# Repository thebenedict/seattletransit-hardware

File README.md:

# Seattle Transit Live

Schematic and PCB for a circuit board map of Seattle area public transit.

[www.seattletransitlive.com](https://www.seattletransitlive.com/)

This board uses an `ESP32-C3` to drive `383` individually addressable `WS2812` LEDs arranged as a stylized regional transit map. The LEDs are split across two chains, and represent live movement across rail, ferry, water taxi, and monorail routes.

## Main Functionality

- Displays a physical transit map with addressable LEDs placed along the network.
- Uses an `ESP32-C3-MINI-1` as the main controller.
- Takes power and USB data over `USB-C`.
- Drives the LED chains through level shifting and a switchable LED power rail.
- Includes an ambient light sensor for auto-dimming in software.

## Repo Contents

- `transit.kicad_sch`, `transit.kicad_pcb`, and the sub-sheet `.kicad_sch` files contain the Rev C schematic and PCB layout.
- `production/` contains fabrication outputs, BOM data, positions, and packaged manufacturing files.
- `tools/` contains scripts and transit GIS/GTFS inputs used to generate LED map configuration data.
- `3d_views/` and `web/public/` contain renders and SVG exports of the board.

## More soon

- Board firmware and supporting cloud service to be published separately.

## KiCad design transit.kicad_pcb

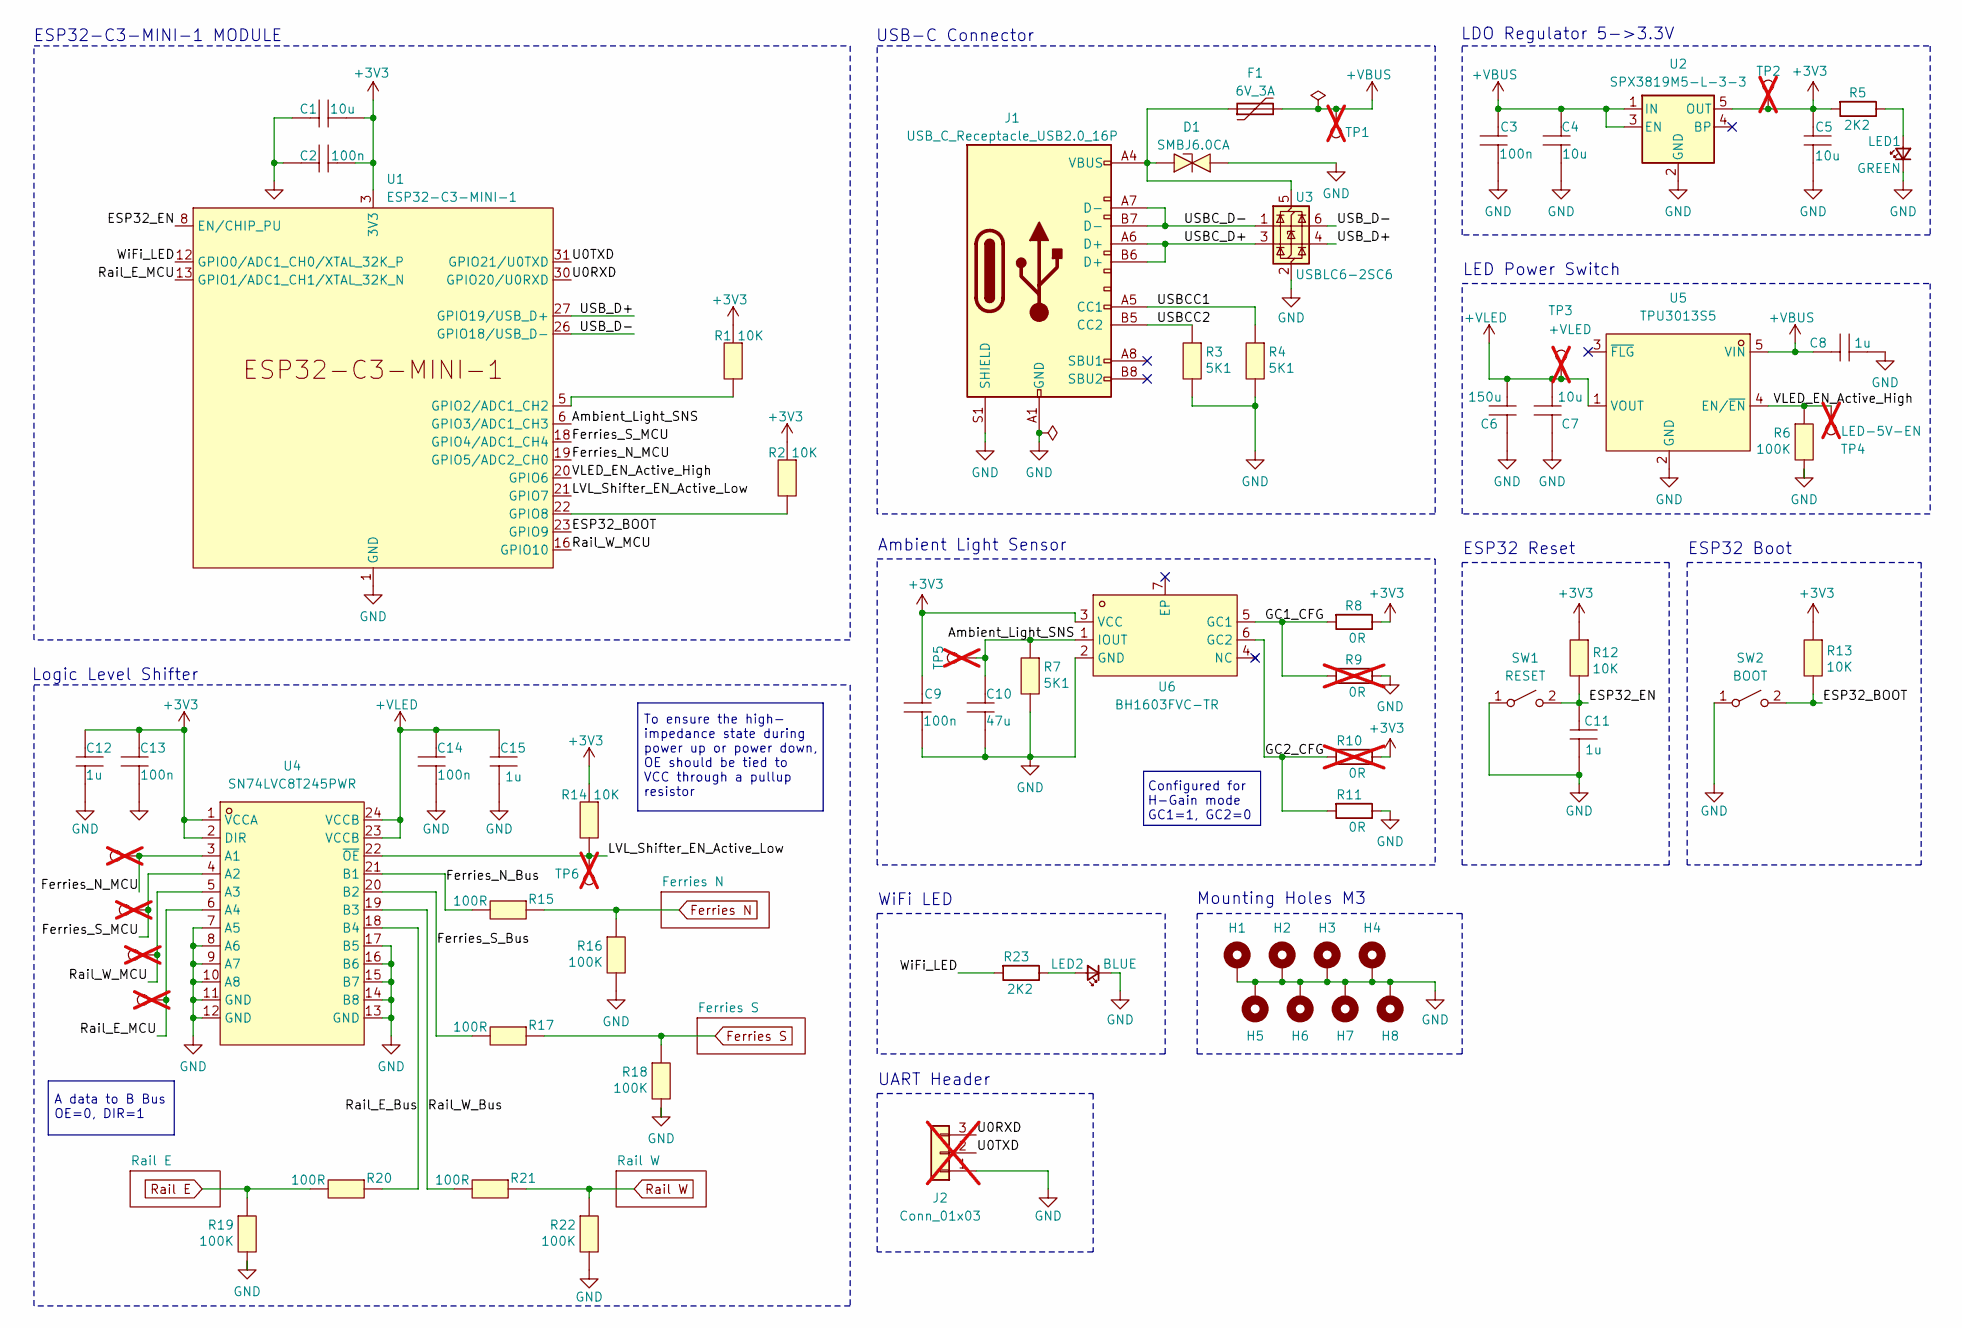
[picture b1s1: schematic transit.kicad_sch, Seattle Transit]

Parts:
C1, C4, C5, C7: 10u; C0805; LCSC Part C95841
C2, C3, C9, C13, C14: 100n; C0603; LCSC Part C1591
C6: 150u; CAP-SMD_L3.5-W2.8; LCSC Part C212682
C8, C11, C12, C15: 1u; C0603; LCSC Part C15849
C10: 47u; C1206; LCSC Part C96123
D1: SMBJ6.0CA; SMB_L4.3-W3.6-LS5.4-BI; LCSC Part C78812
F1: 6V_3A; F1210; LCSC Part C914223
H1, H2, H3, H4, H5, H6, H7, H8: MountingHole_3.2mm_M3_DIN965_Pad
J1: USB_C_Receptacle_USB2.0_16P; USB_C_Receptacle_GCT_USB4105-xx-A_16P_TopMnt_Horizontal; LCSC C393939
J2: Conn_01x03; PinHeader_1x03_P2.54mm_Vertical; not fitted
LED1: GREEN; LED0805-R-RD; LCSC Part C2297
LED2: BLUE; LED0805-R-RD; LCSC Part C2293
R1, R2, R12, R13, R14: 10K; R0603; LCSC Part C25804
R3, R4, R7: 5K1; R0603; LCSC Part C23186
R5, R23: 2K2; R0603; LCSC C4190
R6, R16, R18, R19, R22: 100K; R0603; LCSC Part C25803
R8, R11: 0R; R0603; LCSC C21189
R9, R10: 0R; R0603; LCSC C21189; not fitted
R15, R17, R20, R21: 100R; R0603; LCSC Part C22775
SW1, SW2: SW_SPST; KEY-SMD_L6.2-W3.6-LS8.0_K2-1107ST-A4SW-06; LCSC Part C118141
TP1: +VBUS; TestPoint_Keystone_5005-5009_Compact; not fitted
TP2: +3V3; TestPoint_Keystone_5005-5009_Compact; not fitted
TP3: +VLED; TestPoint_Keystone_5005-5009_Compact; not fitted
TP4: LED-5V-EN; TestPoint_Keystone_5005-5009_Compact; not fitted
TP5: Ambient-Light-SNS; TestPoint_Keystone_5005-5009_Compact; not fitted
TP6: LVL-Shifter-EN; TestPoint_Keystone_5005-5009_Compact; not fitted
TP7: Ferries-S-MCU; TestPoint_Keystone_5005-5009_Compact; not fitted
TP8: Ferries-N-MCU; TestPoint_Keystone_5005-5009_Compact; not fitted
TP9: Rail-W-MCU; TestPoint_Keystone_5005-5009_Compact; not fitted
TP10: Rail-E-MCU; TestPoint_Keystone_5005-5009_Compact; not fitted
U1: ESP32-C3-MINI-1; LCSC C2838502
U2: SPX3819M5-L-3-3; SOT-23-5_L3.0-W1.6-P0.95-LS2.8-BR; LCSC Part C20617301
U3: USBLC6-2SC6; SOT-23-6_L2.9-W1.6-P0.95-LS2.8-BL; LCSC C7519
U4: SN74LVC8T245PWR; TSSOP-24_L7.8-W4.4-P0.65-LS6.4-BL; LCSC Part C27643
U5: TPU3013S5; SOT-23-5_L2.9-W1.6-P0.95-LS2.8-BR; LCSC Part C46472316
U6: BH1603FVC-TR; WSOF-6_L2.6-W1.6-P0.50-BL-EP; LCSC Part C132180

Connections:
+3V3: C1.2, C2.2, C5.1, C9.2, C12.1, C13.2, R1.1, R2.1, R5.2, R8.1, R10.1, R12.1, R13.1, R14.1, TP2.1, U1.3 (3V3), U2.5 (OUT), U4.1 (VCCA), U4.2 (DIR), U6.3 (VCC)
+VBUS: C3.2, C4.1, C8.1, F1.2, TP1.1, U2.1 (IN), U2.3 (EN), U5.5 (VIN)
+VLED: C6.1, C7.1, C14.2, C15.1, TP3.1, U4.23 (VCCB), U4.24 (VCCB), U5.1 (VOUT); also elsewhere on the board
/Ambient_Light_SNS: C10.2, R7.1, TP5.1, U1.6 (GPIO3/ADC1_CH3), U6.1 (IOUT)
/ESP32_BOOT: R13.2, SW2.2 (B), U1.23 (GPIO9)
/ESP32_EN: C11.1, R12.2, SW1.2 (B), U1.8 (EN/CHIP_PU)
/Ferries_N_Bus: R15.2, U4.21 (B1)
/Ferries_N_MCU: TP7.1, U1.19 (GPIO5/ADC2_CH0), U4.3 (A1)
/Ferries_S_Bus: R17.2, U4.20 (B2)
/Ferries_S_MCU: TP8.1, U1.18 (GPIO4/ADC1_CH4), U4.4 (A2)
/GC1_CFG: R8.2, R9.2, U6.5 (GC1)
/GC2_CFG: R10.2, R11.2, U6.6 (GC2)
/LVL_Shifter_EN_Active_Low: R14.2, TP6.1, U1.21 (GPIO7), U4.22 (~OE)
/Rail_E_Bus: R20.1, U4.18 (B4)
/Rail_E_MCU: TP10.1, U1.13 (GPIO1/ADC1_CH1/XTAL_32K_N), U4.6 (A4)
/Rail_W_Bus: R21.2, U4.19 (B3)
/Rail_W_MCU: TP9.1, U1.16 (GPIO10), U4.5 (A3)
/U0RXD: J2.3, U1.30 (GPIO20/U0RXD)
/U0TXD: J2.2, U1.31 (GPIO21/U0TXD)
/USBCC1: J1.A5 (CC1), R4.1
/USBCC2: J1.B5 (CC2), R3.1
/USBC_D+: J1.A6 (D+), J1.B6 (D+), U3.3 (I/O2)
/USBC_D-: J1.A7 (D-), J1.B7 (D-), U3.1 (I/O1)
/USB_D+: U1.27 (GPIO19/USB_D+), U3.4 (I/O2)
/USB_D-: U1.26 (GPIO18/USB_D-), U3.6 (I/O1)
/VLED_EN_Active_High: R6.1, TP4.1, U1.20 (GPIO6), U5.4 (EN/~EN)
/WiFi_LED: R23.2, U1.12 (GPIO0/ADC1_CH0/XTAL_32K_P)
Ferries N: R15.1, R16.1; also elsewhere on the board
Ferries S: R17.1, R18.1; also elsewhere on the board
GND: C1.1, C2.1, C3.1, C4.2, C5.2, C6.2, C7.2, C8.2, C9.1, C10.1, C11.2, C12.2, C13.1, C14.1, C15.2, D1.1, H1.1, H2.1, H3.1, H4.1, H5.1, H6.1, H7.1, H8.1, J1.A1 (GND), J1.A12 (GND), J1.B1 (GND), J1.B12 (GND), J1.S1 (SHIELD), J2.1, LED1.1 (K), LED2.1 (K), R3.2, R4.2, R6.2, R7.2, R9.1, R11.1, R16.2, R18.2, R19.2, R22.2, SW1.1 (A), SW2.1 (A), U1.1 (GND), U1.2 (GND), U1.11 (GND), U1.14 (GND), U1.36 (GND), U1.37 (GND), U1.38 (GND), U1.39 (GND), U1.40 (GND), U1.41 (GND), U1.42 (GND), U1.43 (GND), U1.44 (GND), U1.45 (GND), U1.46 (GND), U1.47 (GND), U1.48 (GND), U1.49 (GND), U1.50 (GND), U1.51 (GND), U1.52 (GND), U1.53 (GND), U2.2 (GND), U3.2 (GND), U4.7 (A5), U4.8 (A6), U4.9 (A7), U4.10 (A8), U4.11 (GND), U4.12 (GND), U4.13 (GND), U4.14 (B8), U4.15 (B7), U4.16 (B6), U4.17 (B5), U5.2 (GND), U6.2 (GND); also elsewhere on the board
unnamed: LED1.2 (A), R5.1
unnamed: LED2.2 (A), R23.1
unnamed: R1.2, U1.5 (GPIO2/ADC1_CH2)
unnamed: R2.2, U1.22 (GPIO8)
unnamed: D1.2, F1.1, J1.A4 (VBUS), J1.A9 (VBUS), J1.B4 (VBUS), J1.B9 (VBUS), U3.5 (VBUS)
Rail E: R19.1, R20.2; also elsewhere on the board
Rail W: R21.1, R22.1; also elsewhere on the board

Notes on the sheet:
Configured for H-Gain mode GC1=1, GC2=0
Ambient Light Sensor
A data to B Bus OE=0, DIR=1
Mounting Holes M3
LDO Regulator 5->3.3V
LED Power Switch
Logic Level Shifter
To ensure the high- impedance state during power up or power down, OE should be tied to VCC through a pullup resistor
ESP32-C3-MINI-1 MODULE
WiFi LED
ESP32 Boot
ESP32 Reset
USB-C Connector
UART Header

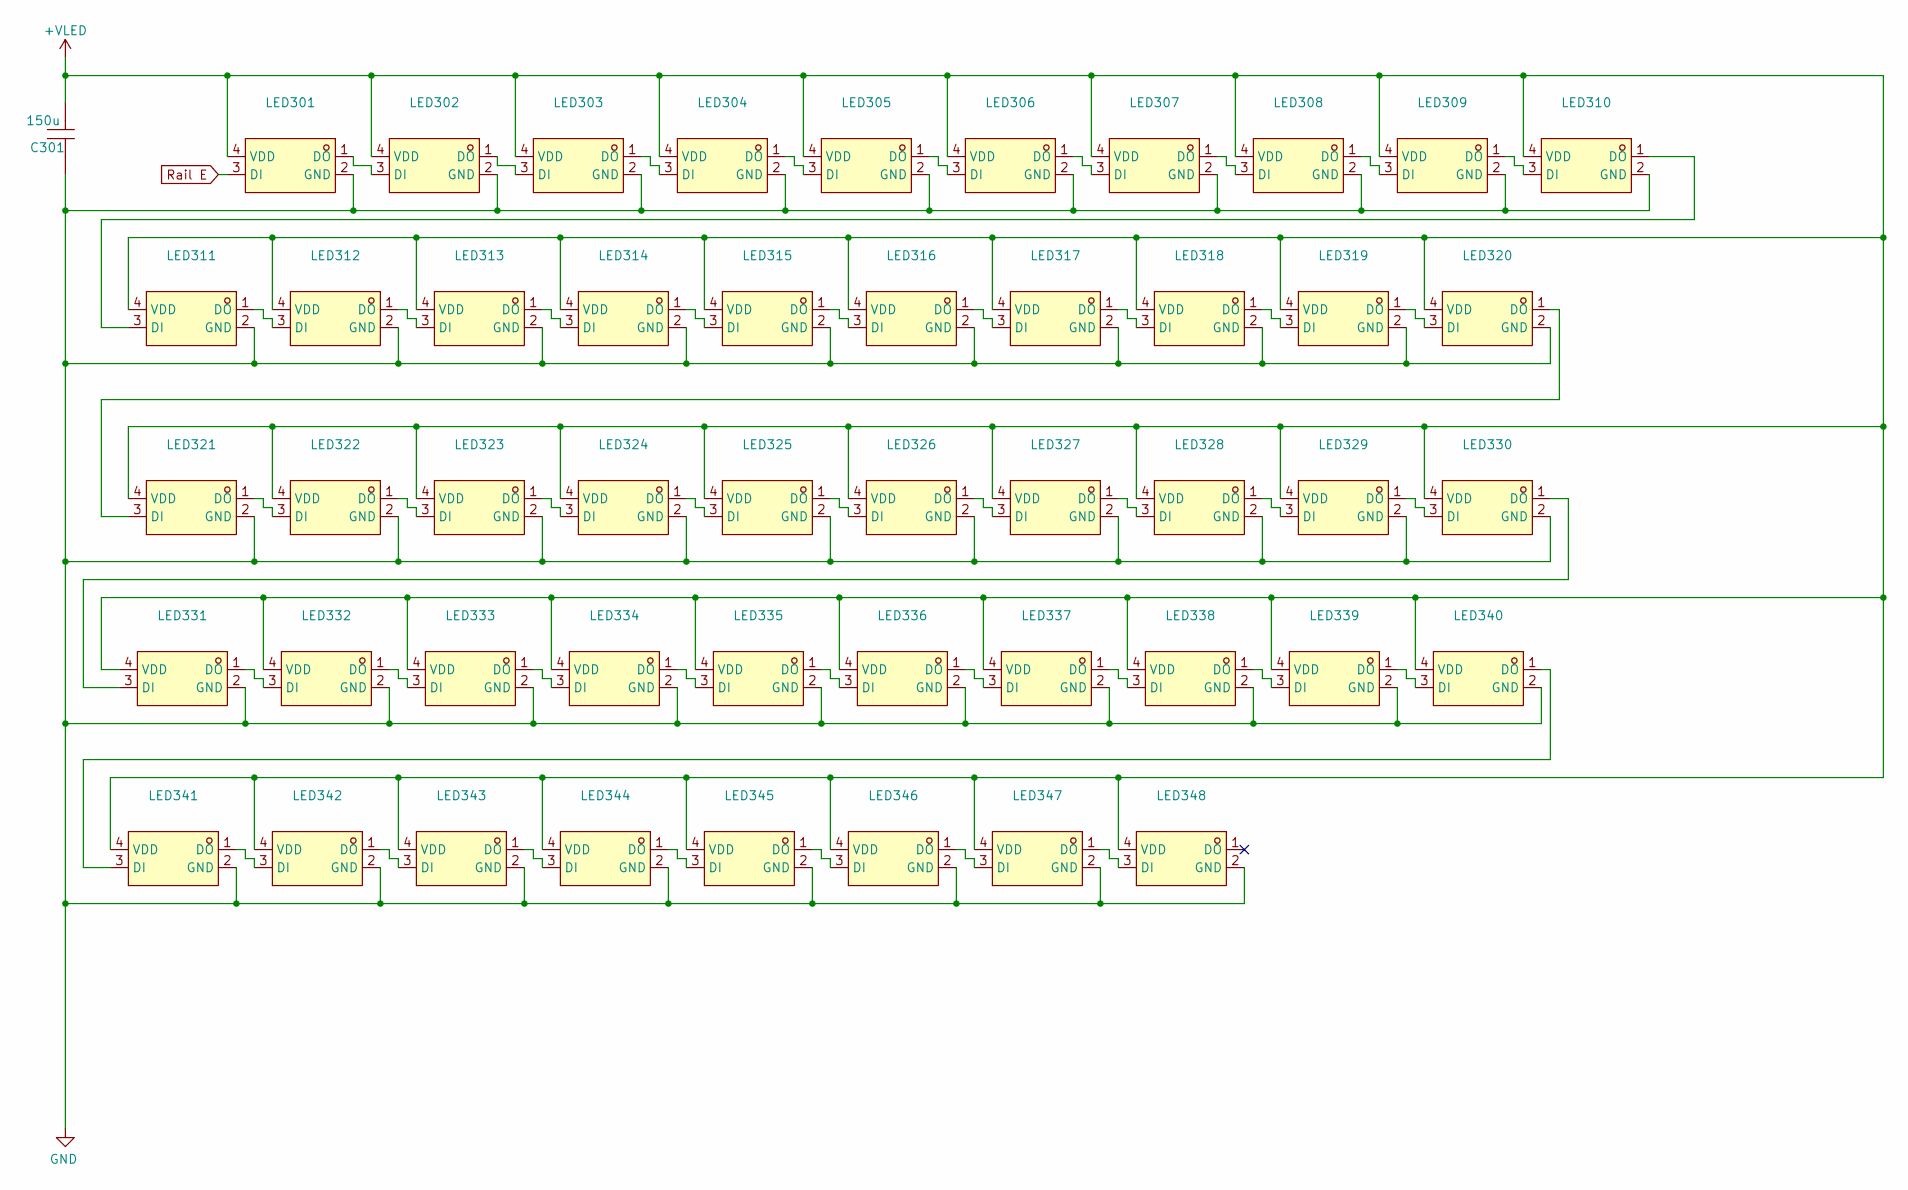
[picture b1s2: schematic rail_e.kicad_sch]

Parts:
C301: 150u; CAP-SMD_L3.5-W2.8; LCSC Part C212682
LED301, LED302, LED303, LED304, LED305, LED306, LED307, LED308, LED309, LED310, LED311, LED312, LED313, LED314, LED315, LED316, LED317, LED318, LED319, LED320, LED321, LED322, LED323, LED324, LED325, LED326, LED327, LED328, LED329, LED330, LED331, LED332, LED333, LED334, LED335, LED336, LED337, LED338, LED339, LED340, LED341, LED342, LED343, LED344, LED345, LED346, LED347, LED348: WS2812B-2020; LED-SMD_4P-L2.0-W2.0-TL_WS2812B-2020; LCSC Part C965555

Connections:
+VLED: C301.1, LED301.4 (VDD), LED302.4 (VDD), LED303.4 (VDD), LED304.4 (VDD), LED305.4 (VDD), LED306.4 (VDD), LED307.4 (VDD), LED308.4 (VDD), LED309.4 (VDD), LED310.4 (VDD), LED311.4 (VDD), LED312.4 (VDD), LED313.4 (VDD), LED314.4 (VDD), LED315.4 (VDD), LED316.4 (VDD), LED317.4 (VDD), LED318.4 (VDD), LED319.4 (VDD), LED320.4 (VDD), LED321.4 (VDD), LED322.4 (VDD), LED323.4 (VDD), LED324.4 (VDD), LED325.4 (VDD), LED326.4 (VDD), LED327.4 (VDD), LED328.4 (VDD), LED329.4 (VDD), LED330.4 (VDD), LED331.4 (VDD), LED332.4 (VDD), LED333.4 (VDD), LED334.4 (VDD), LED335.4 (VDD), LED336.4 (VDD), LED337.4 (VDD), LED338.4 (VDD), LED339.4 (VDD), LED340.4 (VDD), LED341.4 (VDD), LED342.4 (VDD), LED343.4 (VDD), LED344.4 (VDD), LED345.4 (VDD), LED346.4 (VDD), LED347.4 (VDD), LED348.4 (VDD); also elsewhere on the board
GND: C301.2, LED301.2 (GND), LED302.2 (GND), LED303.2 (GND), LED304.2 (GND), LED305.2 (GND), LED306.2 (GND), LED307.2 (GND), LED308.2 (GND), LED309.2 (GND), LED310.2 (GND), LED311.2 (GND), LED312.2 (GND), LED313.2 (GND), LED314.2 (GND), LED315.2 (GND), LED316.2 (GND), LED317.2 (GND), LED318.2 (GND), LED319.2 (GND), LED320.2 (GND), LED321.2 (GND), LED322.2 (GND), LED323.2 (GND), LED324.2 (GND), LED325.2 (GND), LED326.2 (GND), LED327.2 (GND), LED328.2 (GND), LED329.2 (GND), LED330.2 (GND), LED331.2 (GND), LED332.2 (GND), LED333.2 (GND), LED334.2 (GND), LED335.2 (GND), LED336.2 (GND), LED337.2 (GND), LED338.2 (GND), LED339.2 (GND), LED340.2 (GND), LED341.2 (GND), LED342.2 (GND), LED343.2 (GND), LED344.2 (GND), LED345.2 (GND), LED346.2 (GND), LED347.2 (GND), LED348.2 (GND); also elsewhere on the board
unnamed: LED301.1 (DO), LED302.3 (DI)
unnamed: LED302.1 (DO), LED303.3 (DI)
unnamed: LED303.1 (DO), LED304.3 (DI)
unnamed: LED304.1 (DO), LED305.3 (DI)
unnamed: LED305.1 (DO), LED306.3 (DI)
unnamed: LED306.1 (DO), LED307.3 (DI)
unnamed: LED307.1 (DO), LED308.3 (DI)
unnamed: LED308.1 (DO), LED309.3 (DI)
unnamed: LED309.1 (DO), LED310.3 (DI)
unnamed: LED310.1 (DO), LED311.3 (DI)
unnamed: LED311.1 (DO), LED312.3 (DI)
unnamed: LED312.1 (DO), LED313.3 (DI)
unnamed: LED313.1 (DO), LED314.3 (DI)
unnamed: LED314.1 (DO), LED315.3 (DI)
unnamed: LED315.1 (DO), LED316.3 (DI)
unnamed: LED316.1 (DO), LED317.3 (DI)
unnamed: LED317.1 (DO), LED318.3 (DI)
unnamed: LED318.1 (DO), LED319.3 (DI)
unnamed: LED319.1 (DO), LED320.3 (DI)
unnamed: LED320.1 (DO), LED321.3 (DI)
unnamed: LED321.1 (DO), LED322.3 (DI)
unnamed: LED322.1 (DO), LED323.3 (DI)
unnamed: LED323.1 (DO), LED324.3 (DI)
unnamed: LED324.1 (DO), LED325.3 (DI)
unnamed: LED325.1 (DO), LED326.3 (DI)
unnamed: LED326.1 (DO), LED327.3 (DI)
unnamed: LED327.1 (DO), LED328.3 (DI)
unnamed: LED328.1 (DO), LED329.3 (DI)
unnamed: LED329.1 (DO), LED330.3 (DI)
unnamed: LED330.1 (DO), LED331.3 (DI)
unnamed: LED331.1 (DO), LED332.3 (DI)
unnamed: LED332.1 (DO), LED333.3 (DI)
unnamed: LED333.1 (DO), LED334.3 (DI)
unnamed: LED334.1 (DO), LED335.3 (DI)
unnamed: LED335.1 (DO), LED336.3 (DI)
unnamed: LED336.1 (DO), LED337.3 (DI)
unnamed: LED337.1 (DO), LED338.3 (DI)
unnamed: LED338.1 (DO), LED339.3 (DI)
unnamed: LED339.1 (DO), LED340.3 (DI)
unnamed: LED340.1 (DO), LED341.3 (DI)
unnamed: LED341.1 (DO), LED342.3 (DI)
unnamed: LED342.1 (DO), LED343.3 (DI)
unnamed: LED343.1 (DO), LED344.3 (DI)
unnamed: LED344.1 (DO), LED345.3 (DI)
unnamed: LED345.1 (DO), LED346.3 (DI)
unnamed: LED346.1 (DO), LED347.3 (DI)
unnamed: LED347.1 (DO), LED348.3 (DI)
Rail E: LED301.3 (DI); also elsewhere on the board

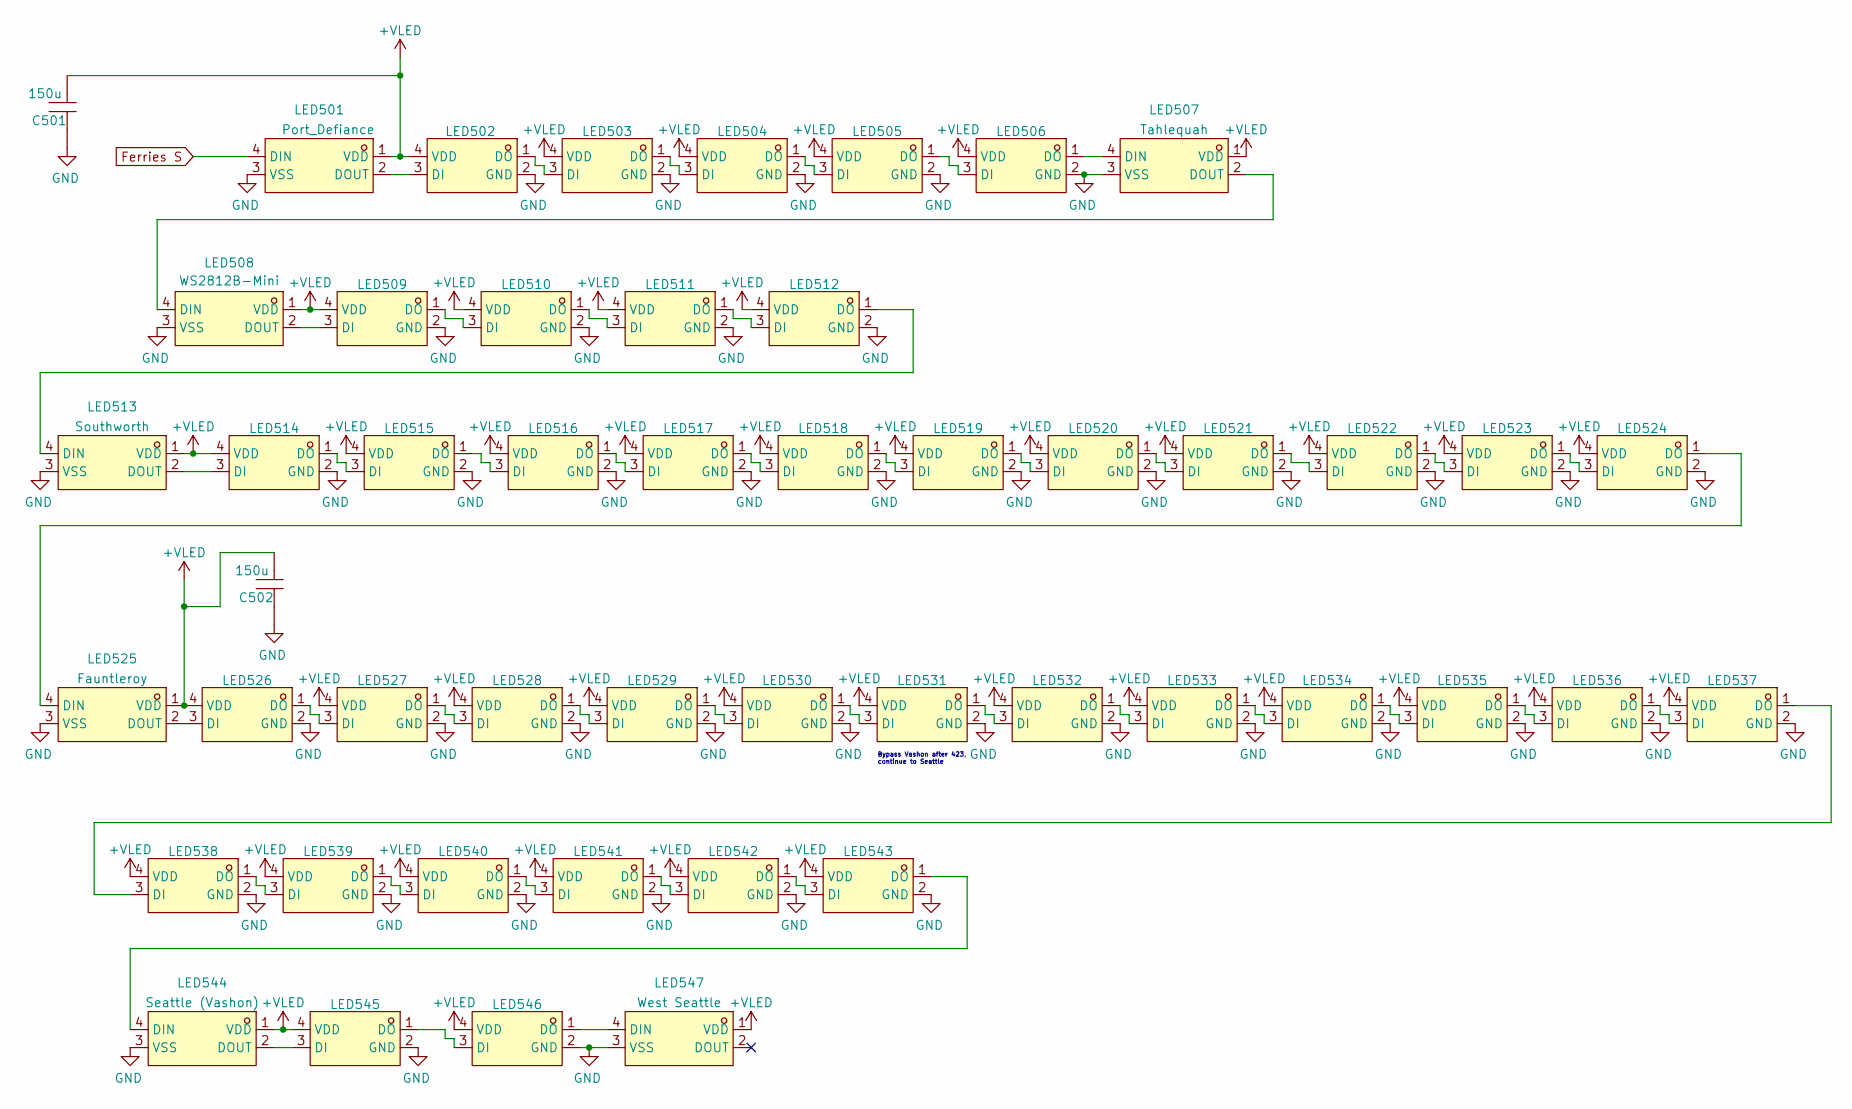
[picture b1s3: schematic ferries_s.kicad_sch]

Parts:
C501, C502: 150u; CAP-SMD_L3.5-W2.8; LCSC Part C212682
LED501, LED507, LED508, LED513, LED525, LED544, LED547: WS2812B-Mini; LED-SMD_4P-L3.5-W3.5-TL_WS2812B; LCSC Part C527089
LED502, LED503, LED504, LED505, LED506, LED509, LED510, LED511, LED512, LED514, LED515, LED516, LED517, LED518, LED519, LED520, LED521, LED522, LED523, LED524, LED526, LED527, LED528, LED529, LED530, LED531, LED532, LED533, LED534, LED535, LED536, LED537, LED538, LED539, LED540, LED541, LED542, LED543, LED545, LED546: WS2812B-2020; LED-SMD_4P-L2.0-W2.0-TL_WS2812B-2020; LCSC Part C965555

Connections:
+VLED: C501.1, C502.1, LED501.1 (VDD), LED502.4 (VDD), LED503.4 (VDD), LED504.4 (VDD), LED505.4 (VDD), LED506.4 (VDD), LED507.1 (VDD), LED508.1 (VDD), LED509.4 (VDD), LED510.4 (VDD), LED511.4 (VDD), LED512.4 (VDD), LED513.1 (VDD), LED514.4 (VDD), LED515.4 (VDD), LED516.4 (VDD), LED517.4 (VDD), LED518.4 (VDD), LED519.4 (VDD), LED520.4 (VDD), LED521.4 (VDD), LED522.4 (VDD), LED523.4 (VDD), LED524.4 (VDD), LED525.1 (VDD), LED526.4 (VDD), LED527.4 (VDD), LED528.4 (VDD), LED529.4 (VDD), LED530.4 (VDD), LED531.4 (VDD), LED532.4 (VDD), LED533.4 (VDD), LED534.4 (VDD), LED535.4 (VDD), LED536.4 (VDD), LED537.4 (VDD), LED538.4 (VDD), LED539.4 (VDD), LED540.4 (VDD), LED541.4 (VDD), LED542.4 (VDD), LED543.4 (VDD), LED544.1 (VDD), LED545.4 (VDD), LED546.4 (VDD), LED547.1 (VDD); also elsewhere on the board
Ferries S: LED501.4 (DIN); also elsewhere on the board
GND: C501.2, C502.2, LED501.3 (VSS), LED502.2 (GND), LED503.2 (GND), LED504.2 (GND), LED505.2 (GND), LED506.2 (GND), LED507.3 (VSS), LED508.3 (VSS), LED509.2 (GND), LED510.2 (GND), LED511.2 (GND), LED512.2 (GND), LED513.3 (VSS), LED514.2 (GND), LED515.2 (GND), LED516.2 (GND), LED517.2 (GND), LED518.2 (GND), LED519.2 (GND), LED520.2 (GND), LED521.2 (GND), LED522.2 (GND), LED523.2 (GND), LED524.2 (GND), LED525.3 (VSS), LED526.2 (GND), LED527.2 (GND), LED528.2 (GND), LED529.2 (GND), LED530.2 (GND), LED531.2 (GND), LED532.2 (GND), LED533.2 (GND), LED534.2 (GND), LED535.2 (GND), LED536.2 (GND), LED537.2 (GND), LED538.2 (GND), LED539.2 (GND), LED540.2 (GND), LED541.2 (GND), LED542.2 (GND), LED543.2 (GND), LED544.3 (VSS), LED545.2 (GND), LED546.2 (GND), LED547.3 (VSS); also elsewhere on the board
unnamed: LED501.2 (DOUT), LED502.3 (DI)
unnamed: LED502.1 (DO), LED503.3 (DI)
unnamed: LED503.1 (DO), LED504.3 (DI)
unnamed: LED504.1 (DO), LED505.3 (DI)
unnamed: LED505.1 (DO), LED506.3 (DI)
unnamed: LED506.1 (DO), LED507.4 (DIN)
unnamed: LED507.2 (DOUT), LED508.4 (DIN)
unnamed: LED508.2 (DOUT), LED509.3 (DI)
unnamed: LED509.1 (DO), LED510.3 (DI)
unnamed: LED510.1 (DO), LED511.3 (DI)
unnamed: LED511.1 (DO), LED512.3 (DI)
unnamed: LED512.1 (DO), LED513.4 (DIN)
unnamed: LED513.2 (DOUT), LED514.3 (DI)
unnamed: LED514.1 (DO), LED515.3 (DI)
unnamed: LED515.1 (DO), LED516.3 (DI)
unnamed: LED516.1 (DO), LED517.3 (DI)
unnamed: LED517.1 (DO), LED518.3 (DI)
unnamed: LED518.1 (DO), LED519.3 (DI)
unnamed: LED519.1 (DO), LED520.3 (DI)
unnamed: LED520.1 (DO), LED521.3 (DI)
unnamed: LED521.1 (DO), LED522.3 (DI)
unnamed: LED522.1 (DO), LED523.3 (DI)
unnamed: LED523.1 (DO), LED524.3 (DI)
unnamed: LED524.1 (DO), LED525.4 (DIN)
unnamed: LED525.2 (DOUT), LED526.3 (DI)
unnamed: LED526.1 (DO), LED527.3 (DI)
unnamed: LED527.1 (DO), LED528.3 (DI)
unnamed: LED528.1 (DO), LED529.3 (DI)
unnamed: LED529.1 (DO), LED530.3 (DI)
unnamed: LED530.1 (DO), LED531.3 (DI)
unnamed: LED531.1 (DO), LED532.3 (DI)
unnamed: LED532.1 (DO), LED533.3 (DI)
unnamed: LED533.1 (DO), LED534.3 (DI)
unnamed: LED534.1 (DO), LED535.3 (DI)
unnamed: LED535.1 (DO), LED536.3 (DI)
unnamed: LED536.1 (DO), LED537.3 (DI)
unnamed: LED537.1 (DO), LED538.3 (DI)
unnamed: LED538.1 (DO), LED539.3 (DI)
unnamed: LED539.1 (DO), LED540.3 (DI)
unnamed: LED540.1 (DO), LED541.3 (DI)
unnamed: LED541.1 (DO), LED542.3 (DI)
unnamed: LED542.1 (DO), LED543.3 (DI)
unnamed: LED543.1 (DO), LED544.4 (DIN)
unnamed: LED544.2 (DOUT), LED545.3 (DI)
unnamed: LED545.1 (DO), LED546.3 (DI)
unnamed: LED546.1 (DO), LED547.4 (DIN)

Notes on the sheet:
Bypass Vashon after 423, continue to Seattle

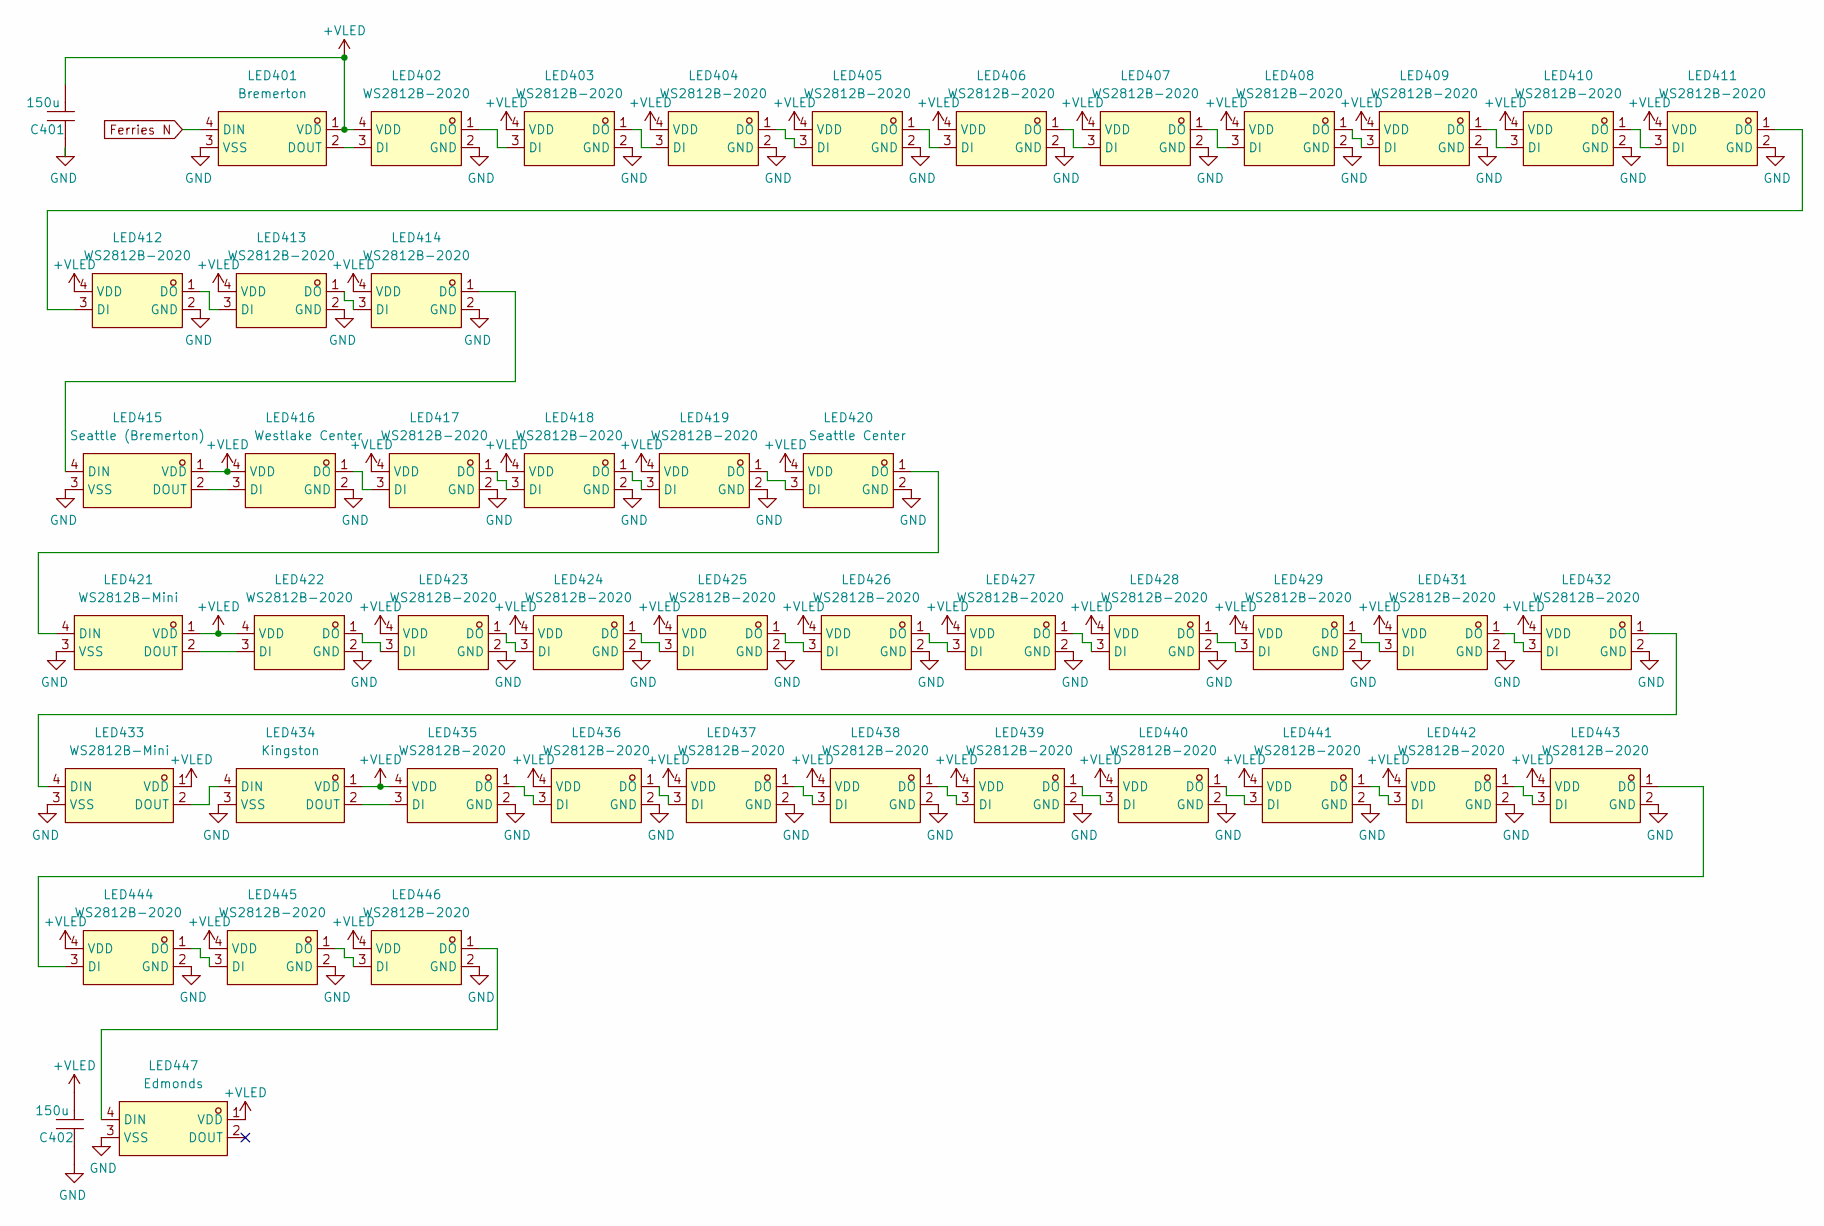
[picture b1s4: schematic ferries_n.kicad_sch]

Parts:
C401, C402: 150u; CAP-SMD_L3.5-W2.8; LCSC Part C212682
LED401, LED415, LED421, LED433, LED434, LED447: WS2812B-Mini; LED-SMD_4P-L3.5-W3.5-TL_WS2812B; LCSC Part C527089
LED402, LED403, LED404, LED405, LED406, LED407, LED408, LED409, LED410, LED411, LED412, LED413, LED414, LED416, LED417, LED418, LED419, LED420, LED422, LED423, LED424, LED425, LED426, LED427, LED428, LED429, LED431, LED432, LED435, LED436, LED437, LED438, LED439, LED440, LED441, LED442, LED443, LED444, LED445, LED446: WS2812B-2020; LED-SMD_4P-L2.0-W2.0-TL_WS2812B-2020; LCSC Part C965555

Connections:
+VLED: C401.1, C402.1, LED401.1 (VDD), LED402.4 (VDD), LED403.4 (VDD), LED404.4 (VDD), LED405.4 (VDD), LED406.4 (VDD), LED407.4 (VDD), LED408.4 (VDD), LED409.4 (VDD), LED410.4 (VDD), LED411.4 (VDD), LED412.4 (VDD), LED413.4 (VDD), LED414.4 (VDD), LED415.1 (VDD), LED416.4 (VDD), LED417.4 (VDD), LED418.4 (VDD), LED419.4 (VDD), LED420.4 (VDD), LED421.1 (VDD), LED422.4 (VDD), LED423.4 (VDD), LED424.4 (VDD), LED425.4 (VDD), LED426.4 (VDD), LED427.4 (VDD), LED428.4 (VDD), LED429.4 (VDD), LED431.4 (VDD), LED432.4 (VDD), LED433.1 (VDD), LED434.1 (VDD), LED435.4 (VDD), LED436.4 (VDD), LED437.4 (VDD), LED438.4 (VDD), LED439.4 (VDD), LED440.4 (VDD), LED441.4 (VDD), LED442.4 (VDD), LED443.4 (VDD), LED444.4 (VDD), LED445.4 (VDD), LED446.4 (VDD), LED447.1 (VDD); also elsewhere on the board
Ferries N: LED401.4 (DIN); also elsewhere on the board
GND: C401.2, C402.2, LED401.3 (VSS), LED402.2 (GND), LED403.2 (GND), LED404.2 (GND), LED405.2 (GND), LED406.2 (GND), LED407.2 (GND), LED408.2 (GND), LED409.2 (GND), LED410.2 (GND), LED411.2 (GND), LED412.2 (GND), LED413.2 (GND), LED414.2 (GND), LED415.3 (VSS), LED416.2 (GND), LED417.2 (GND), LED418.2 (GND), LED419.2 (GND), LED420.2 (GND), LED421.3 (VSS), LED422.2 (GND), LED423.2 (GND), LED424.2 (GND), LED425.2 (GND), LED426.2 (GND), LED427.2 (GND), LED428.2 (GND), LED429.2 (GND), LED431.2 (GND), LED432.2 (GND), LED433.3 (VSS), LED434.3 (VSS), LED435.2 (GND), LED436.2 (GND), LED437.2 (GND), LED438.2 (GND), LED439.2 (GND), LED440.2 (GND), LED441.2 (GND), LED442.2 (GND), LED443.2 (GND), LED444.2 (GND), LED445.2 (GND), LED446.2 (GND), LED447.3 (VSS); also elsewhere on the board
unnamed: LED401.2 (DOUT), LED402.3 (DI)
unnamed: LED402.1 (DO), LED403.3 (DI)
unnamed: LED403.1 (DO), LED404.3 (DI)
unnamed: LED404.1 (DO), LED405.3 (DI)
unnamed: LED405.1 (DO), LED406.3 (DI)
unnamed: LED406.1 (DO), LED407.3 (DI)
unnamed: LED407.1 (DO), LED408.3 (DI)
unnamed: LED408.1 (DO), LED409.3 (DI)
unnamed: LED409.1 (DO), LED410.3 (DI)
unnamed: LED410.1 (DO), LED411.3 (DI)
unnamed: LED411.1 (DO), LED412.3 (DI)
unnamed: LED412.1 (DO), LED413.3 (DI)
unnamed: LED413.1 (DO), LED414.3 (DI)
unnamed: LED414.1 (DO), LED415.4 (DIN)
unnamed: LED415.2 (DOUT), LED416.3 (DI)
unnamed: LED416.1 (DO), LED417.3 (DI)
unnamed: LED417.1 (DO), LED418.3 (DI)
unnamed: LED418.1 (DO), LED419.3 (DI)
unnamed: LED419.1 (DO), LED420.3 (DI)
unnamed: LED420.1 (DO), LED421.4 (DIN)
unnamed: LED421.2 (DOUT), LED422.3 (DI)
unnamed: LED422.1 (DO), LED423.3 (DI)
unnamed: LED423.1 (DO), LED424.3 (DI)
unnamed: LED424.1 (DO), LED425.3 (DI)
unnamed: LED425.1 (DO), LED426.3 (DI)
unnamed: LED426.1 (DO), LED427.3 (DI)
unnamed: LED427.1 (DO), LED428.3 (DI)
unnamed: LED428.1 (DO), LED429.3 (DI)
unnamed: LED429.1 (DO), LED431.3 (DI)
unnamed: LED431.1 (DO), LED432.3 (DI)
unnamed: LED432.1 (DO), LED433.4 (DIN)
unnamed: LED433.2 (DOUT), LED434.4 (DIN)
unnamed: LED434.2 (DOUT), LED435.3 (DI)
unnamed: LED435.1 (DO), LED436.3 (DI)
unnamed: LED436.1 (DO), LED437.3 (DI)
unnamed: LED437.1 (DO), LED438.3 (DI)
unnamed: LED438.1 (DO), LED439.3 (DI)
unnamed: LED439.1 (DO), LED440.3 (DI)
unnamed: LED440.1 (DO), LED441.3 (DI)
unnamed: LED441.1 (DO), LED442.3 (DI)
unnamed: LED442.1 (DO), LED443.3 (DI)
unnamed: LED443.1 (DO), LED444.3 (DI)
unnamed: LED444.1 (DO), LED445.3 (DI)
unnamed: LED445.1 (DO), LED446.3 (DI)
unnamed: LED446.1 (DO), LED447.4 (DIN)

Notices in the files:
transit.kicad_pcb:
© 2026 Charles Street Labs
